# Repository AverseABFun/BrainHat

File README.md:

# BrainHat
BrainHat is a project I'm working on to make a cost-effective, affordable EEG headset to better the lives of people with. The current status is an EEG headset that can read one electrode and store that onto a MicroSD card in a Raspberry Pi Zero W. The current headset contains the custom amplifier(files for which in this project), a Raspberry Pi Zero W, and my flipper zero. Code for both of the microcontrollers is in https://github.com/AverseABFun/brainhat-code.

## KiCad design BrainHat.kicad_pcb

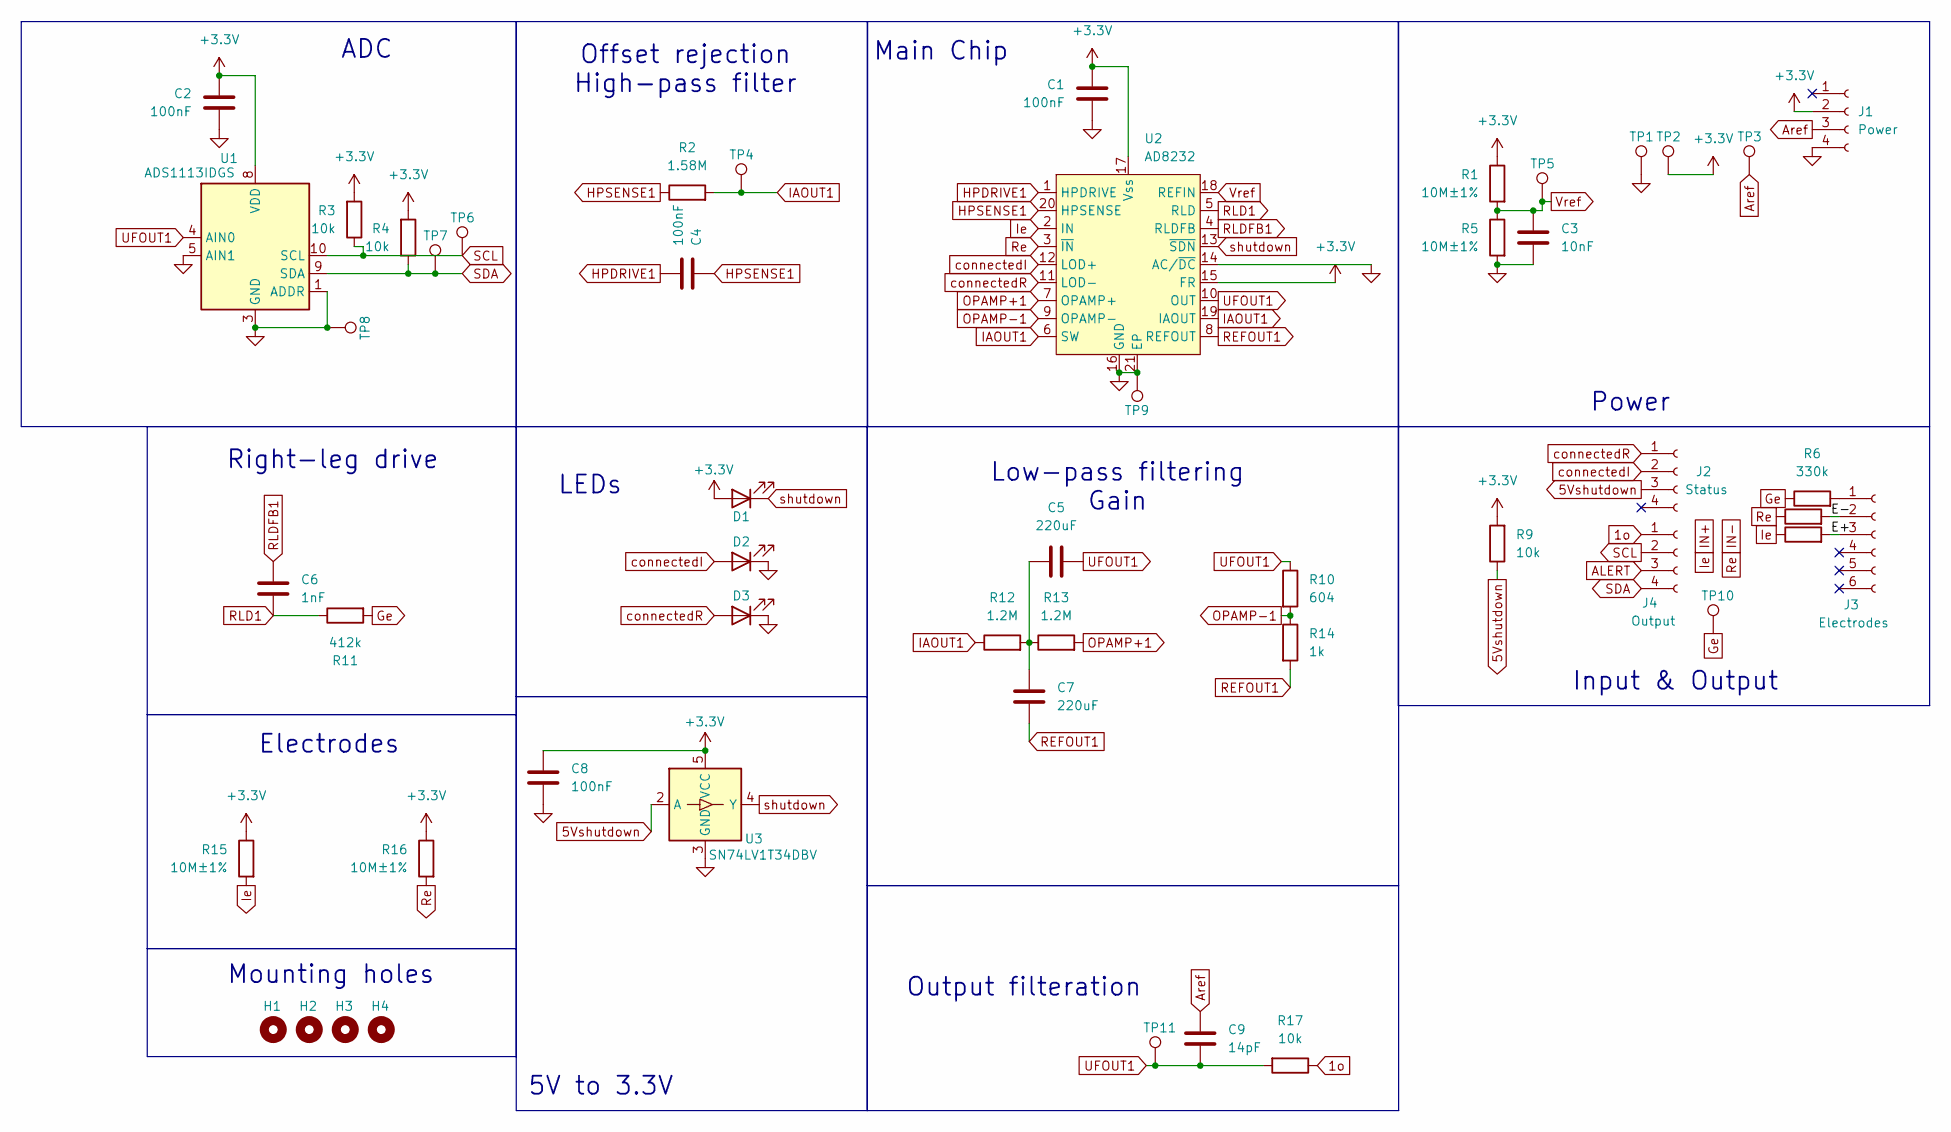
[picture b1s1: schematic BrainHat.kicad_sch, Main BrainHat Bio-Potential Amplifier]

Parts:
C1, C2, C4, C8: 100nF; C_1210_3225Metric; LCSC Part # C569766
C3: 10nF; C_0805_2012Metric; LCSC Part # C5448895
C5, C7: 220uF; C_1206_3216Metric; LCSC Part # C412252
C6: 1nF; C_Disc_D6.0mm_W4.4mm_P5.00mm; LCSC Part # C2887268
C9: 14pF; C_0402_1005Metric; LCSC Part # C3037644
D1: XL-1608UBC-04; LED_0603_1608Metric; LCSC Part # C965807
D2, D3: XL-2012UWC; LED_0805_2012Metric; LCSC Part # C965818
H1, H2, H3, H4: MountingHole; MountingHole_2.2mm_M2
J1: Power; PinSocket_1x04_P2.54mm_Vertical; LCSC Part # C5116530
J2: Status; PinSocket_1x04_P2.54mm_Vertical; LCSC Part # C5116530
J3: Electrodes; PinHeader_1x06_P2.54mm_Vertical; LCSC Part # C7509518
J4: Output; PinSocket_1x04_P2.54mm_Vertical; LCSC Part # C5116530
R1, R5, R15, R16: 10M±1%; R_0402_1005Metric; LCSC Part # C2933065
R2: 1.58M; R_0402_1005Metric; LCSC Part # C368345
R3, R4, R9, R17: 10k; R_1206_3216Metric; LCSC Part # C17902
R6, R7, R8: 330k; R_0402_1005Metric; LCSC Part # C3017599
R10: 604; R_0402_1005Metric; LCSC Part # C2998094
R11: 412k; R_0402_1005Metric; LCSC Part # C5126037
R12, R13: 1.2M; R_0402_1005Metric; LCSC Part # C43675
R14: 1k; R_0402_1005Metric; LCSC Part # C2906899
TP1, TP2, TP3, TP4, TP5, TP6, TP7, TP8, TP9, TP10, TP11: TestPoint; TestPoint_Pad_D1.5mm
U1: ADS1113IDGS; TSSOP-10_3x3mm_P0.5mm
U2: AD8232; LFCSP-20-1EP_4x4mm_P0.5mm_EP2.5x2.5mm; LCSC Part # C43216
U3: SN74LV1T34DBV; SOT-23-5; LCSC Part # C100024

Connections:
1o: J4.1, R17.1
5Vshutdown: J2.3, R9.1, U3.2 (A)
+3.3V: C1.1, C2.1, C8.1, D1.2 (A), J1.2, R1.1, R3.2, R4.2, R9.2, R15.1, R16.1, TP2.1, U1.8 (VDD), U2.15 (FR), U2.17 (Vss), U3.5 (VCC)
/E+: J3.3, R8.2
/E-: J3.2, R7.2
ALERT: J4.3
Aref: C9.1, J1.3, TP3.1
GND: C1.2, C2.2, C3.2, C8.2, D2.1 (K), D3.1 (K), J1.4, R5.2, TP1.1, TP8.1, TP9.1, U1.1 (ADDR), U1.3 (GND), U1.5 (AIN1), U2.14 (AC/~DC), U2.16 (GND), U2.21 (EP), U3.3 (GND)
Ge: R6.1, R11.2, TP10.1
HPDRIVE1: C4.2, U2.1 (HPDRIVE)
HPSENSE1: C4.1, R2.1, U2.20 (HPSENSE)
IAOUT1: R2.2, R12.1, TP4.1, U2.6 (SW), U2.19 (IAOUT)
IN+: R8.1, R15.2, U2.2 (IN)
IN-: R7.1, R16.2, U2.3 (~IN)
unnamed: C5.1, C7.1, R12.2, R13.1
unnamed: J3.1, R6.2
OPAMP+1: R13.2, U2.7 (OPAMP+)
OPAMP-1: R10.2, R14.1, U2.9 (OPAMP-)
REFOUT1: C7.2, R14.2, U2.8 (REFOUT)
RLD1: C6.2, R11.1, U2.5 (RLD)
RLDFB1: C6.1, U2.4 (RLDFB)
SCL: J4.2, R3.1, TP6.1, U1.10 (SCL)
SDA: J4.4, R4.1, TP7.1, U1.9 (SDA)
UFOUT1: C5.2, C9.2, R10.1, R17.2, TP11.1, U1.4 (AIN0), U2.10 (OUT)
Vref: C3.1, R1.2, R5.1, TP5.1, U2.18 (REFIN)
connectedI: D2.2 (A), J2.2, U2.12 (LOD+)
connectedR: D3.2 (A), J2.1, U2.11 (LOD-)
shutdown: D1.1 (K), U2.13 (~SDN), U3.4 (Y)

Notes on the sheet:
5V to 3.3V
Low-pass filtering Gain
Mounting holes
Power
Output filteration
ADC
Right-leg drive
LEDs
Input & Output
Main Chip
Offset rejection High-pass filter
Electrodes

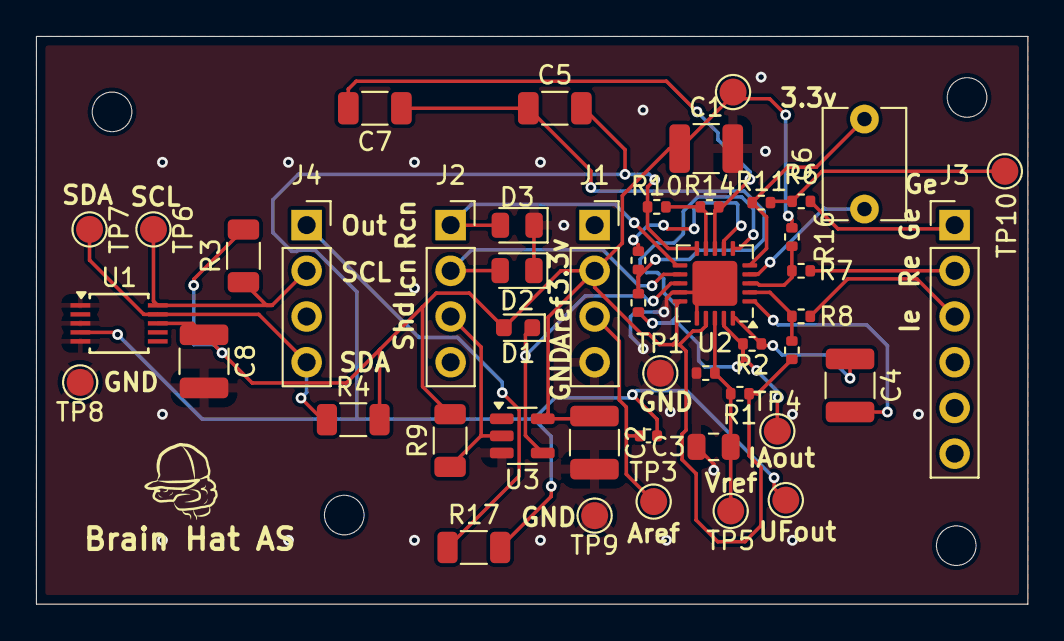
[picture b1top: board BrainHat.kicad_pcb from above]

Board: 2 copper layers, 55.1 x 31.5 mm, 51 parts (0 on the bottom side), 27 nets.

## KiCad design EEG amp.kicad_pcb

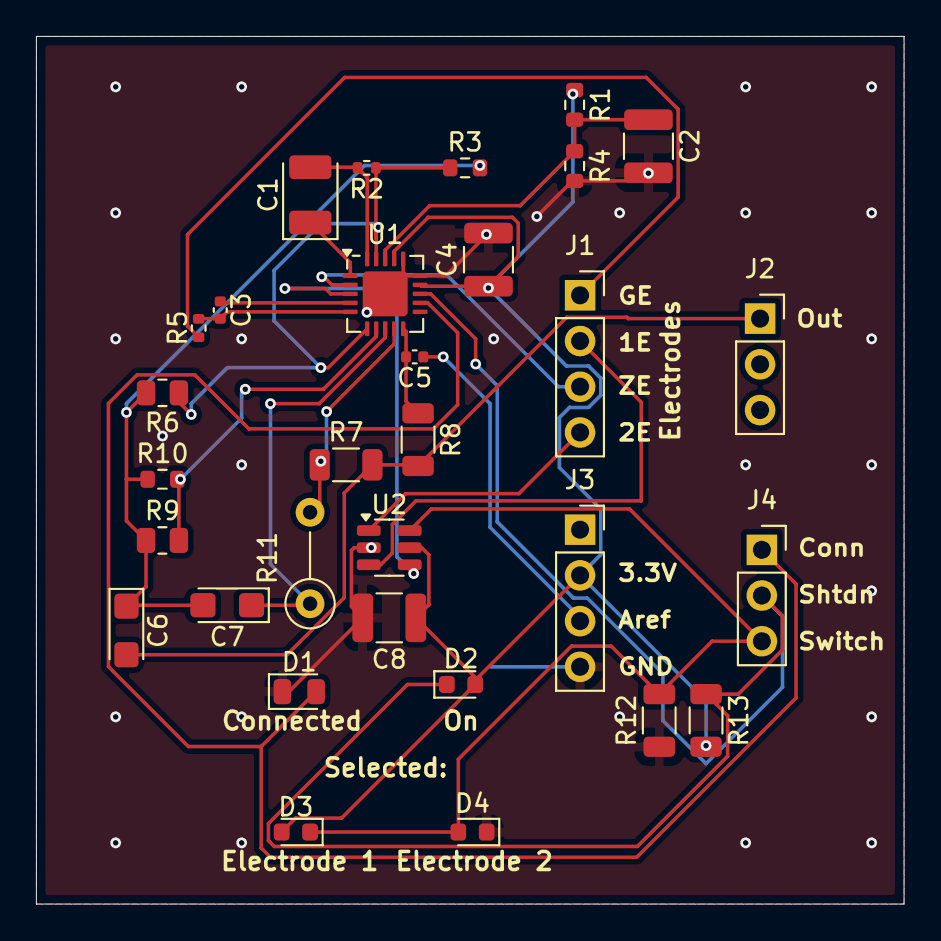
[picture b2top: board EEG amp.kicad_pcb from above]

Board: 2 copper layers, 48.2 x 48.2 mm, 31 parts (0 on the bottom side), 23 nets.

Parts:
C1: CA45-B6R3K107T; CP_EIA-3528-21_Kemet-B
C2, C4, C8: ECHU1C104GX5; C_1210_3225Metric
C3: CC0402JRX7R9BB102; C_0402_1005Metric
C5: 0402CG140J500NT; C_0402_1005Metric
C6, C7: CA45-A010K106T; CP_EIA-3216-12_Kemet-S
D1: XL-2012UWC; LED_0805_2012Metric
D2: XL-1608UBC-04; LED_0603_1608Metric
D3, D4: XL-1608UGC-04; LED_0603_1608Metric
J1: Electrodes; PinSocket_1x04_P2.54mm_Vertical
J2: Output; PinSocket_1x03_P2.54mm_Vertical
J3: Power; PinSocket_1x04_P2.54mm_Vertical
J4: Status; PinSocket_1x03_P2.54mm_Vertical
R1, R4: ARG03BTC1002; R_0603_1608Metric
R2, R5: SCR0402J330K; R_0402_1005Metric
R3, R10: 0603WAD3302T5E; R_0603_1608Metric
R6, R9: ARG05DTC1600; R_0805_2012Metric
R7, R8, R12, R13: 1206W4F1002T5E; R_1206_3216Metric
R11: CF1/6W-7.5KΩ±5%T52; R_Axial_DIN0207_L6.3mm_D2.5mm_P5.08mm_Vertical
U1: AD8232; LFCSP-20-1EP_4x4mm_P0.5mm_EP2.5x2.5mm
U2: TS5A3159ADBVR; SOT-23-6

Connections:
1e: J1.2, U2.3
1o: C6.2, J2.1, R7.2, R8.2
2e: J1.4, U2.1
+3.3V: C4.1, C8.1, D2.2 (A), D3.2 (A), J3.2, R1.1, R13.2, U1.14 (AC/~DC), U1.17 (Vss), U2.5 (V+)
Aref: C5.1, J3.3
GND: C2.2, C4.2, C8.2, D1.1 (K), D4.1 (K), J3.4, R4.2, R12.1, U1.15 (FR), U1.16 (GND), U1.21 (EP), U2.2 (GND)
Ge: J1.1, R5.1
HPDRIVE1: C1.1, U1.1 (HPDRIVE)
HPSENSE1: C1.2, R2.2, U1.20 (HPSENSE)
IAOUT1: R2.1, R3.1, R6.1, U1.6 (SW), U1.19 (IAOUT)
Ie: U1.3 (~IN), U2.4
unnamed: C6.1, C7.2, R3.2, R6.2, R9.1, R10.1
OPAMP+1: R9.2, R10.2, U1.7 (OPAMP+)
OPAMP-1: R7.1, R11.2, U1.9 (OPAMP-)
REFOUT1: C7.1, R11.1, U1.8 (REFOUT)
RLD1: C3.2, R5.2, U1.5 (RLD)
RLDFB1: C3.1, U1.4 (RLDFB)
UFOUT1: C5.2, R8.1, U1.10 (OUT)
Vref: C2.1, R1.2, R4.1, U1.18 (REFIN)
Ze: J1.3, U1.2 (IN)
connected1: D1.2 (A), J4.1, U1.12 (LOD+)
shutdown: D2.1 (K), J4.2, R13.1, U1.13 (~SDN)
switch: D3.1 (K), D4.2 (A), J4.3, R12.2, U2.6

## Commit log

2024-08-09 added files
2024-08-09 Added AD8232 symbol
2024-08-09 Organized and added mux
2024-08-09 added lock files to gitignore and changed the mux a bit
2024-08-09 removed lock file
2024-08-09 Organization and status LEDs
2024-08-09 rearranged
2024-08-10 Organized better and got some tips from from a professional PCB designer :3
2024-08-10 slightly rearranged things
2024-08-10 Started work on the PCB
2024-08-10 Designed PCB and apparently did something to the schematic
2024-08-10 Changed gitignore, reorganized schematic a bit, connected EP to ground, and updated the symbol
2024-09-01 Messed with schematic and(I think) finished PCB
2024-09-01 Ran DRC and changed ground plane
2024-09-01 Exported various files for OnBoard
2024-09-01 Production files
2024-09-03 adjusted many things, including, apparently, the footprint for one of the resistors
2024-09-15 Renamed everything
2024-09-27 Started work on version 2
2024-09-28 YAAAA
2024-09-28 YAAAAY R2(unreviewed)
2024-09-28 Silkscreen
2024-09-29 Change license to my MFPL 1B
2024-10-01 Redid PCB again
2024-10-13 Made a variety of changes
2024-10-13 deleted some out-of-date files
2024-10-13 Exported step file and deleted another out-of-date file.
2024-10-13 too much info last time
2024-10-29 made many a change
